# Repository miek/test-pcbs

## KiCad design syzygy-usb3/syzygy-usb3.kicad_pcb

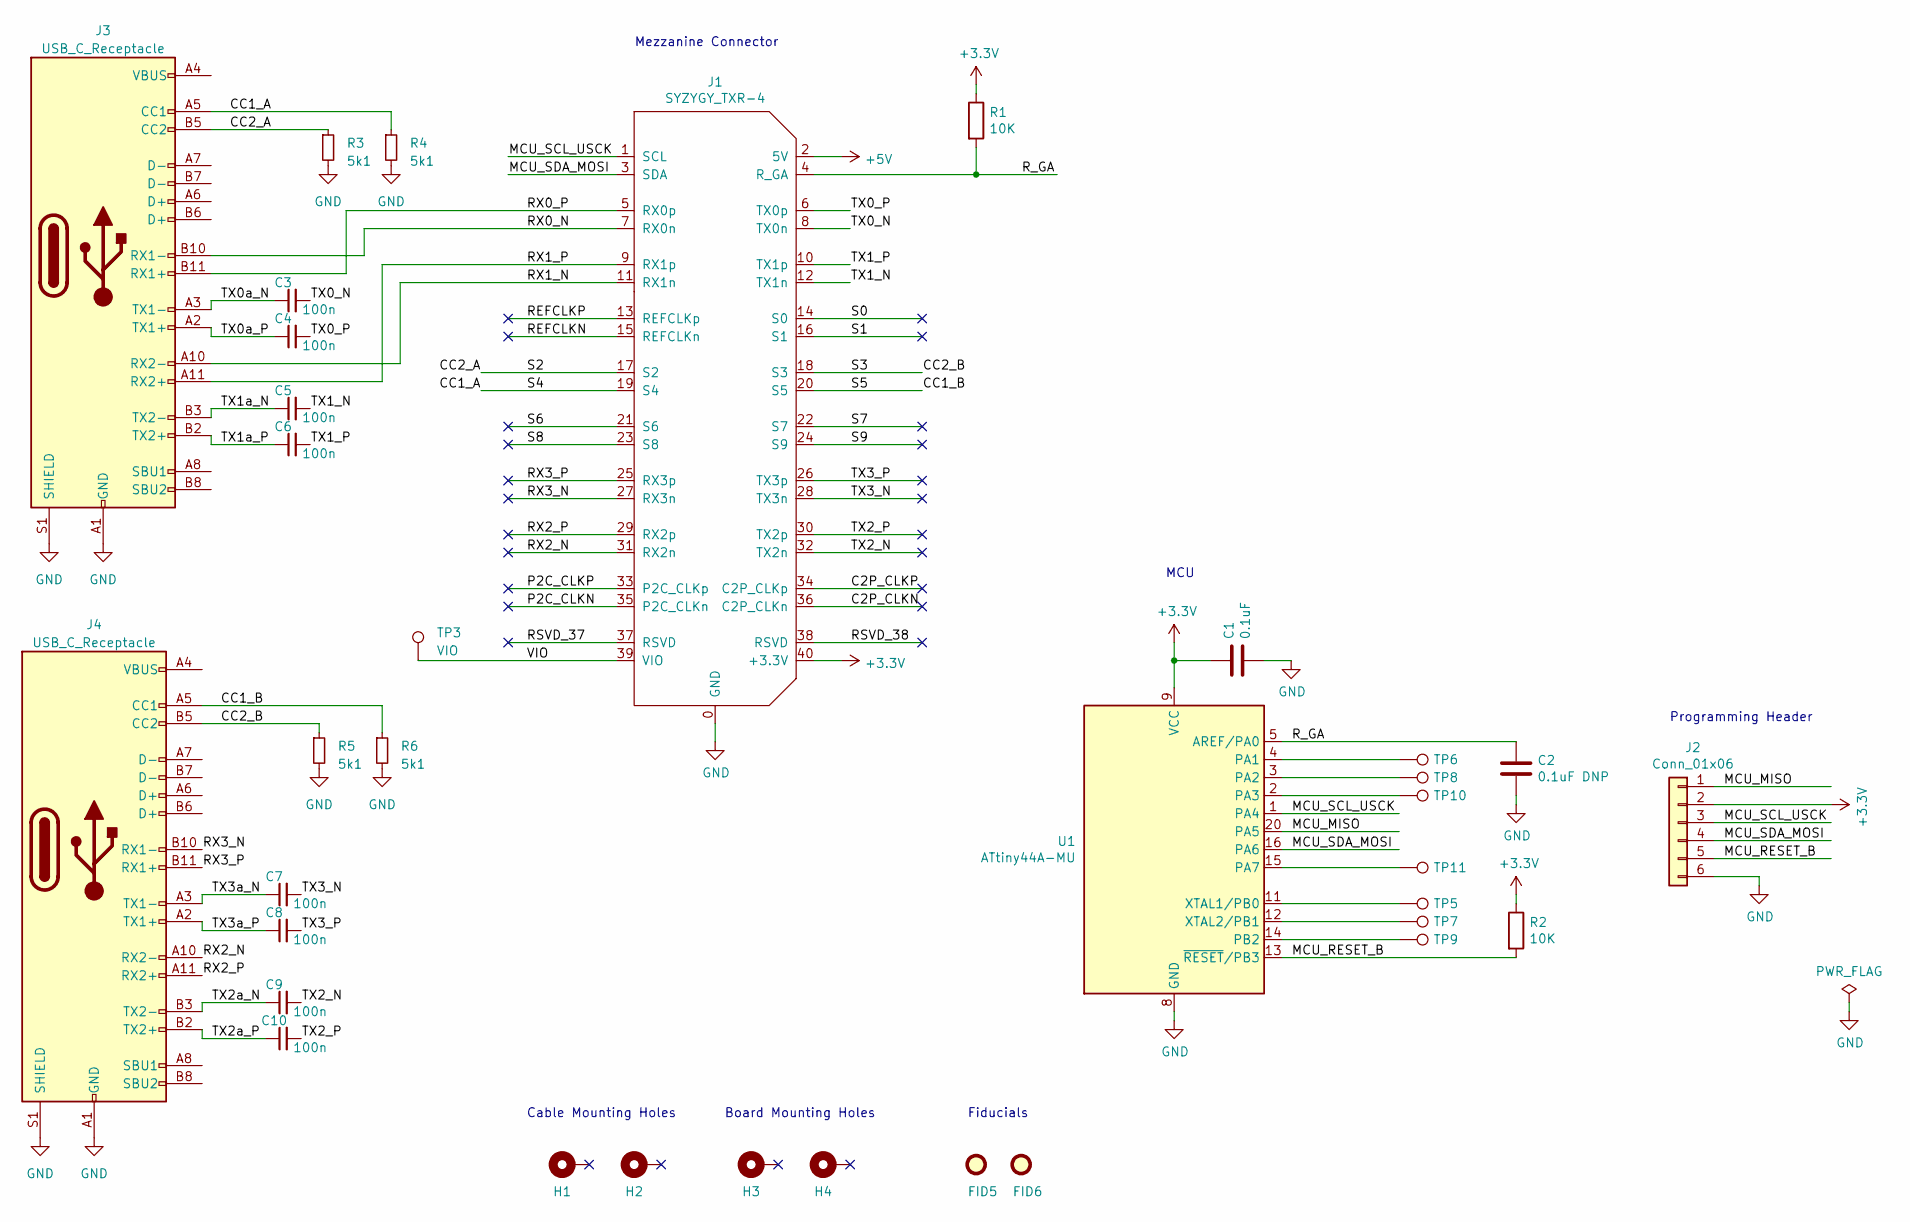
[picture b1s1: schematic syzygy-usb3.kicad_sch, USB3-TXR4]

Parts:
C1: 0.1uF; C_0402_1005Metric
C2: 0.1uF DNP; C_0402_1005Metric
C3, C4, C5, C6, C7, C8, C9, C10: 100n; C_0201_0603Metric
FID5, FID6: Fiducial; Fiducial_1mm_Mask2mm
H1, H2, H3, H4: MountingHole_Pad; MountingHole_3.2mm_M3_6.5mm_Pad_TopBottom
J1: SYZYGY_TXR-4; QTH-020-01-F-D-DP-A; Manufacturer_PN QTH-020-01-F-D-DP-A
J2: Conn_01x06; Tag-Connect_TC2030-IDC-FP_2x03_P1.27mm_Vertical
J3, J4: USB_C_Receptacle; USB_C_Receptacle_Amphenol_12401610E4-2A
R1, R2: 10K; R_0402_1005Metric
R3, R4, R5, R6: 5k1; R_0402_1005Metric
TP3: VIO; TestPoint_Pad_D1.0mm
TP5, TP6, TP7, TP8, TP9, TP10, TP11: TestPoint; TestPoint-20mil
U1: ATtiny44A-MU; QFN-24-4x4mm; Manufacturer_PN ATTINY44A-MU

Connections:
+3V3: C1.1, J1.40 (+3.3V), J2.2, R1.1, R2.1, U1.9 (VCC)
+5V: J1.2 (5V)
/C2P_CLKN: J1.36 (C2P_CLKn)
/C2P_CLKP: J1.34 (C2P_CLKp)
/CC1_A: J1.19 (S4), J3.A5 (CC1), R4.1
/CC1_B: J1.20 (S5), J4.A5 (CC1), R6.1
/CC2_A: J1.17 (S2), J3.B5 (CC2), R3.1
/CC2_B: J1.18 (S3), J4.B5 (CC2), R5.1
/MCU_MISO: J2.1, U1.20 (PA5)
/MCU_RESET_B: J2.5, R2.2, U1.13 (~RESET/PB3)
/MCU_SCL_USCK: J1.1 (SCL), J2.3, U1.1 (PA4)
/MCU_SDA_MOSI: J1.3 (SDA), J2.4, U1.16 (PA6)
/P2C_CLKN: J1.35 (P2C_CLKn)
/P2C_CLKP: J1.33 (P2C_CLKp)
/REFCLKN: J1.15 (REFCLKn)
/REFCLKP: J1.13 (REFCLKp)
/RSVD_37: J1.37 (RSVD)
/RSVD_38: J1.38 (RSVD)
/RX0_N: J1.7 (RX0n), J3.B10 (RX1-)
/RX0_P: J1.5 (RX0p), J3.B11 (RX1+)
/RX1_N: J1.11 (RX1n), J3.A10 (RX2-)
/RX1_P: J1.9 (RX1p), J3.A11 (RX2+)
/RX2_N: J1.31 (RX2n), J4.A10 (RX2-)
/RX2_P: J1.29 (RX2p), J4.A11 (RX2+)
/RX3_N: J1.27 (RX3n), J4.B10 (RX1-)
/RX3_P: J1.25 (RX3p), J4.B11 (RX1+)
/R_GA: C2.1, J1.4 (R_GA), R1.2, U1.5 (AREF/PA0)
/S0: J1.14 (S0)
/S1: J1.16 (S1)
/S6: J1.21 (S6)
/S7: J1.22 (S7)
/S8: J1.23 (S8)
/S9: J1.24 (S9)
/TX0_N: C3.2, J1.8 (TX0n)
/TX0_P: C4.2, J1.6 (TX0p)
/TX0a_N: C3.1, J3.A3 (TX1-)
/TX0a_P: C4.1, J3.A2 (TX1+)
/TX1_N: C5.2, J1.12 (TX1n)
/TX1_P: C6.2, J1.10 (TX1p)
/TX1a_N: C5.1, J3.B3 (TX2-)
/TX1a_P: C6.1, J3.B2 (TX2+)
/TX2_N: C9.2, J1.32 (TX2n)
/TX2_P: C10.2, J1.30 (TX2p)
/TX2a_N: C9.1, J4.B3 (TX2-)
/TX2a_P: C10.1, J4.B2 (TX2+)
/TX3_N: C7.2, J1.28 (TX3n)
/TX3_P: C8.2, J1.26 (TX3p)
/TX3a_N: C7.1, J4.A3 (TX1-)
/TX3a_P: C8.1, J4.A2 (TX1+)
/VIO: J1.39 (VIO), TP3.1
GND: C1.2, C2.2, J1.0 (GND), J2.6, J3.A1 (GND), J3.A12 (GND), J3.B1 (GND), J3.B12 (GND), J3.S1 (SHIELD), J4.A1 (GND), J4.A12 (GND), J4.B1 (GND), J4.B12 (GND), J4.S1 (SHIELD), R3.2, R4.2, R5.2, R6.2, U1.8 (GND), U1.21 (GND)
unnamed: J3.A4 (VBUS), J3.A9 (VBUS), J3.B4 (VBUS), J3.B9 (VBUS)
unnamed: J4.A4 (VBUS), J4.A9 (VBUS), J4.B4 (VBUS), J4.B9 (VBUS)
unnamed: TP6.1, U1.4 (PA1)
unnamed: TP8.1, U1.3 (PA2)
unnamed: TP10.1, U1.2 (PA3)
unnamed: TP11.1, U1.15 (PA7)
unnamed: TP9.1, U1.14 (PB2)
unnamed: TP5.1, U1.11 (XTAL1/PB0)
unnamed: TP7.1, U1.12 (XTAL2/PB1)

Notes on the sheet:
Programming Header
Board Mounting Holes
MCU
Mezzanine Connector
Cable Mounting Holes
Fiducials

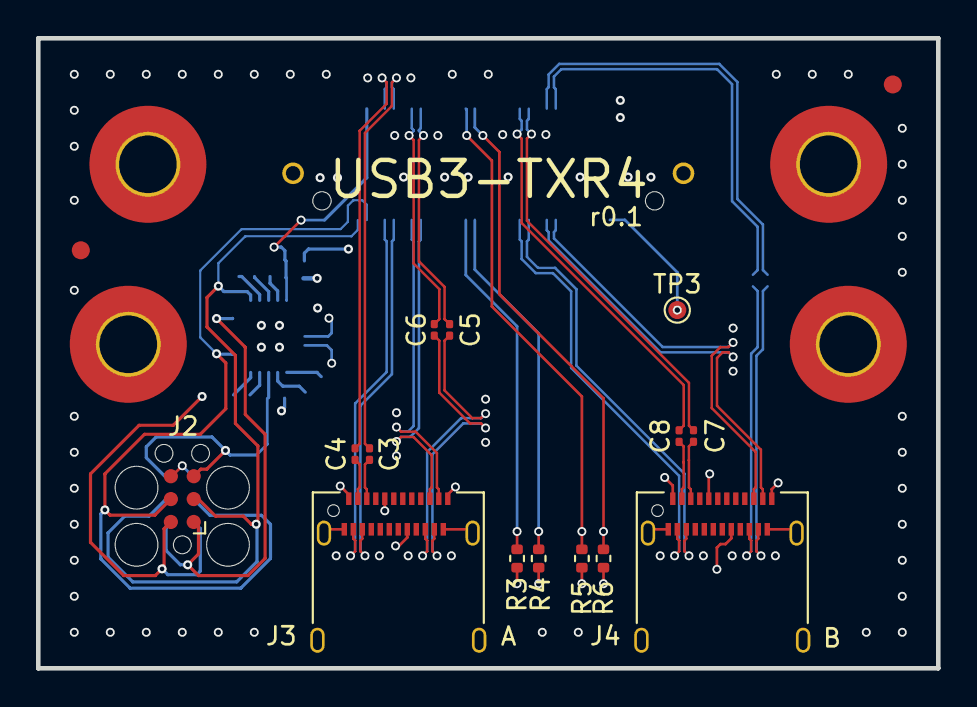
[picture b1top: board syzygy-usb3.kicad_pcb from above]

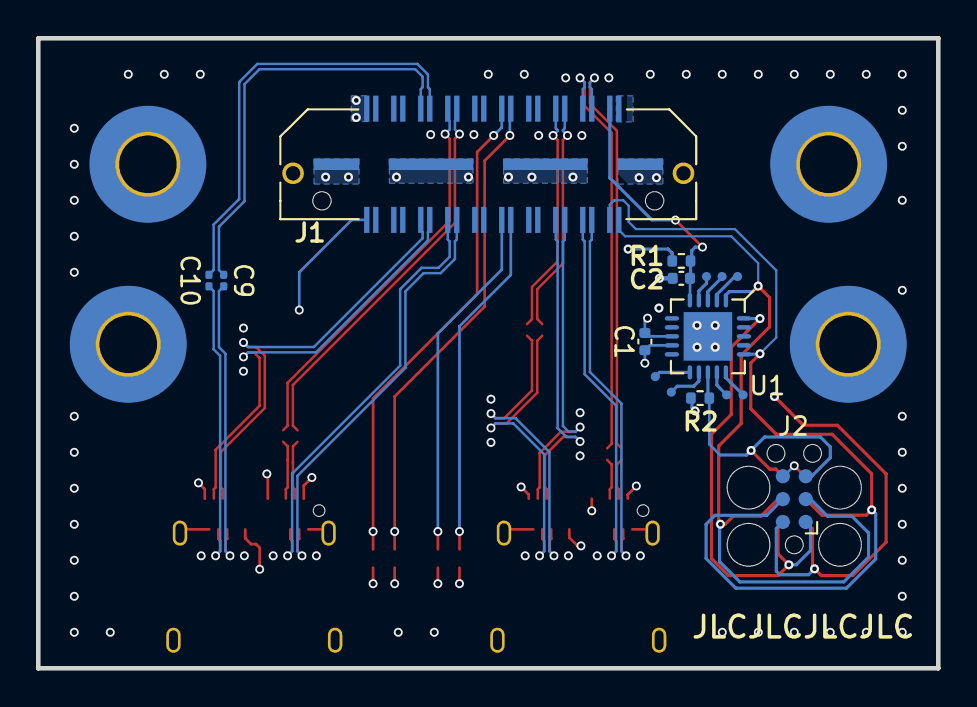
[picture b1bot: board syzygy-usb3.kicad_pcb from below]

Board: 6 copper layers, 50.0 x 35.0 mm, 35 parts (15 on the bottom side), 45 nets.

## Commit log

2023-11-01 add SYZYGY USB3 breakout
